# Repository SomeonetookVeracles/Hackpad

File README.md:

# Hackpad
The hackpad for hack club highway

I'm a big man, and when I use my dinky 60% keyboard I often find that my hands wrap around to the ends of it when resting, this is obviously uncomfortable, and when combined with the fact it doesn't come with a tilda (yes, seriously), I decided to make a hackpad that's more ergonomic, and with a more interesting shape than just **square**

|Reference                  |Qty|Value                  |DNP|Exclude from BOM|Exclude from Board|Footprint                                                                          |Datasheet                                                          |
|---------------------------|---|-----------------------|---|----------------|------------------|-----------------------------------------------------------------------------------|-------------------------------------------------------------------|
|D1,D2,D3,D4                |4  |SK6805                 |   |                |                  |LED_SMD:LED_SK6805_PLCC4_2.4x2.7mm_P1.3mm                                          |https://cdn-shop.adafruit.com/product-files/3484/3484_Datasheet.pdf|
|SW1,SW2,SW3,SW4,SW6,SW7,SW8|7  |SW_Push_45deg          |   |                |                  |PCM_Switch_Keyboard_Cherry_MX:SW_Cherry_MX_PCB_1.00u                               |~                                                                  |
|SW5                        |1  |RotaryEncoder_Switch_MP|   |                |                  |Rotary_Encoder:RotaryEncoder_Alps_EC11E-Switch_Vertical_H20mm_CircularMountingHoles|~                                                                  |
|U1                         |1  |XIAO-RP2040-DIP        |   |                |                  |Seeed Studio XIAO Series Library:XIAO-RP2040-SMD                                   |                                                                   |

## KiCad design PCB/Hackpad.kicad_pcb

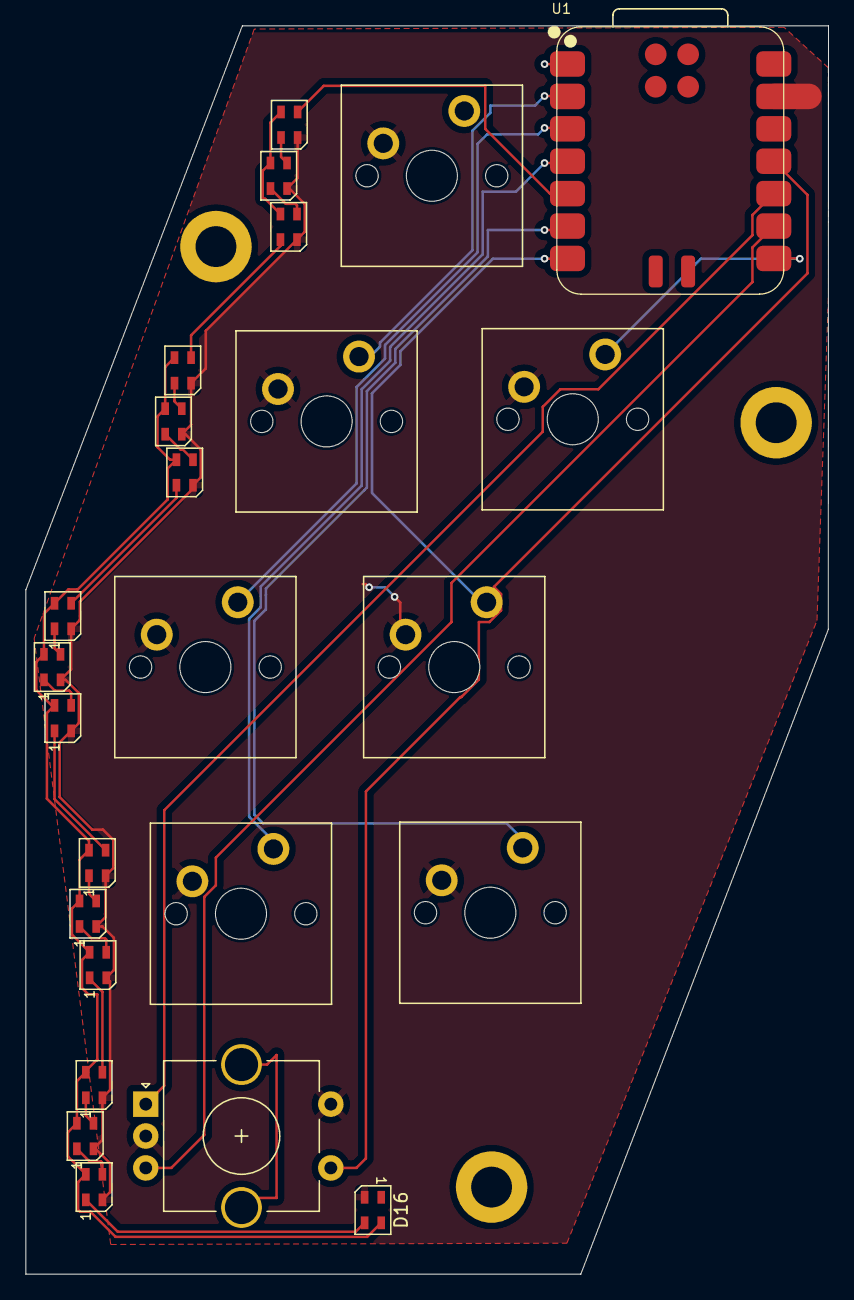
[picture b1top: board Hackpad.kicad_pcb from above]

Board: 2 copper layers, 62.9 x 97.8 mm, 25 parts (0 on the bottom side), 28 nets.

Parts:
D1, D2, D3, D4, D5, D6, D7, D8, D9, D10, D11, D12, D13, D14, D15, D16: SK6805; LED_SK6805_PLCC4_2.4x2.7mm_P1.3mm
SW1, SW2, SW3, SW4, SW6, SW7, SW8: SW_Push_45deg; SW_Cherry_MX_PCB_1.00u
SW5: RotaryEncoder_Switch_MP; RotaryEncoder_Alps_EC11E-Switch_Vertical_H20mm_CircularMoun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
U1: XIAO-RP2040-DIP; XIAO-RP2040-SMD

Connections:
+5V: D1.4 (VDD), D2.4 (VDD), D3.4 (VDD), D4.4 (VDD), D5.4 (VDD), D6.4 (VDD), D7.4 (VDD), D8.4 (VDD), D9.4 (VDD), D10.4 (VDD), D11.4 (VDD), D12.4 (VDD), D13.4 (VDD), D14.4 (VDD), D15.4 (VDD), D16.4 (VDD), U1.14 (VBUS)
GND: D1.2 (VSS), D2.2 (VSS), D3.2 (VSS), D4.2 (VSS), D5.2 (VSS), D6.2 (VSS), D7.2 (VSS), D8.2 (VSS), D9.2 (VSS), D10.2 (VSS), D11.2 (VSS), D12.2 (VSS), D13.2 (VSS), D14.2 (VSS), D15.2 (VSS), D16.2 (VSS), SW1.1, SW2.1, SW3.1, SW4.1, SW5.C, SW5.S2, SW6.1, SW7.1, SW8.1, U1.13 (GND)
unnamed: D1.3 (DIN), U1.5 (GPIO6/SDA)
unnamed: D1.1 (DOUT), D2.3 (DIN)
unnamed: D2.1 (DOUT), D3.3 (DIN)
unnamed: D3.1 (DOUT), D4.3 (DIN)
unnamed: D4.1 (DOUT), D5.3 (DIN)
unnamed: D5.1 (DOUT), D6.3 (DIN)
unnamed: D6.1 (DOUT), D7.3 (DIN)
unnamed: D7.1 (DOUT), D8.3 (DIN)
unnamed: D8.1 (DOUT), D9.3 (DIN)
unnamed: D9.1 (DOUT), D10.3 (DIN)
unnamed: D10.1 (DOUT), D11.3 (DIN)
unnamed: D11.1 (DOUT), D12.3 (DIN)
unnamed: D12.1 (DOUT), D13.3 (DIN)
unnamed: D13.1 (DOUT), D14.3 (DIN)
unnamed: D14.1 (DOUT), D15.3 (DIN)
unnamed: D15.1 (DOUT), D16.3 (DIN)
unnamed: SW7.2, U1.7 (GPIO0/TX)
unnamed: SW8.2, U1.8 (GPIO1/RX)
unnamed: SW5.B, U1.9 (GPIO2/SCK)
unnamed: SW5.S1, U1.11 (GPIO3/MOSI)
unnamed: SW5.A, U1.10 (GPIO4/MISO)
unnamed: SW6.2, U1.6 (GPIO7/SCL)
unnamed: SW1.2, U1.1 (GPIO26/ADC0/A0)
unnamed: SW2.2, U1.2 (GPIO27/ADC1/A1)
unnamed: SW3.2, U1.3 (GPIO28/ADC2/A2)
unnamed: SW4.2, U1.4 (GPIO29/ADC3/A3)

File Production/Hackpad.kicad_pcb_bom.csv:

Designator,Quantity,Value,Footprint,Package,MPN,DNP,Mount_Type,Description
"D1, D10, D11, D12, D13, D14, D15, D16, D2, D3, D4, D5, D6, D7, D8, D9",16,SK6805,LED_SK6805_PLCC4_2.4x2.7mm_P1.3mm,,,,smt,RGB LED with integrated controller
"SW1, SW2, SW3, SW4, SW6, SW7, SW8",7,SW_Push_45deg,SW_Cherry_MX_PCB_1.00u,,,,tht,"Push button switch, normally open, two pins, 45° tilted"
SW5,1,RotaryEncoder_Switch_MP,RotaryEncoder_Alps_EC11E-Switch_Vertical_H20mm_CircularMountingHoles,,,,tht,"Rotary encoder, dual channel, incremental quadrate outputs, with switch and MP Pin"
U1,1,XIAO-RP2040-DIP,XIAO-RP2040-SMD,,,,tht,

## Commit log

2025-07-31 Resubmission
2025-08-01 Fixed!
    e
